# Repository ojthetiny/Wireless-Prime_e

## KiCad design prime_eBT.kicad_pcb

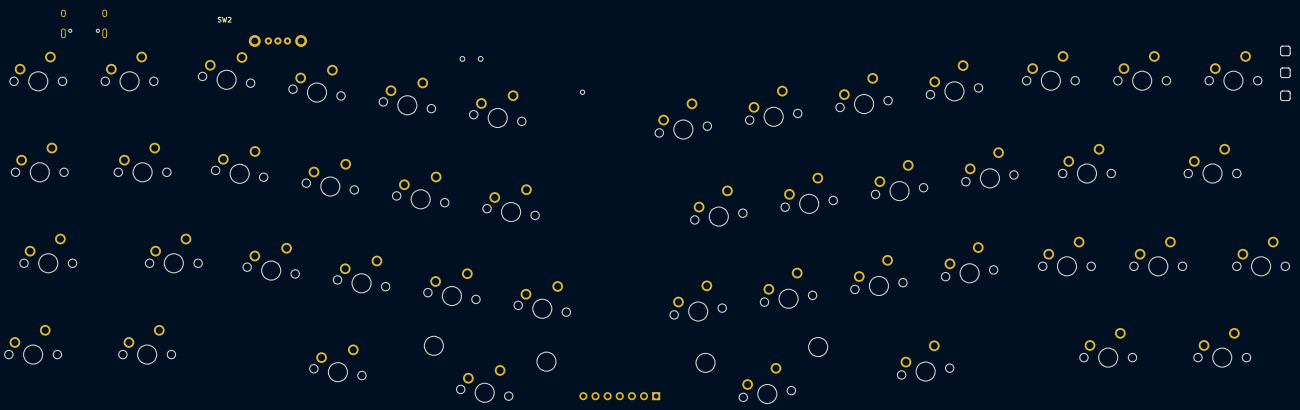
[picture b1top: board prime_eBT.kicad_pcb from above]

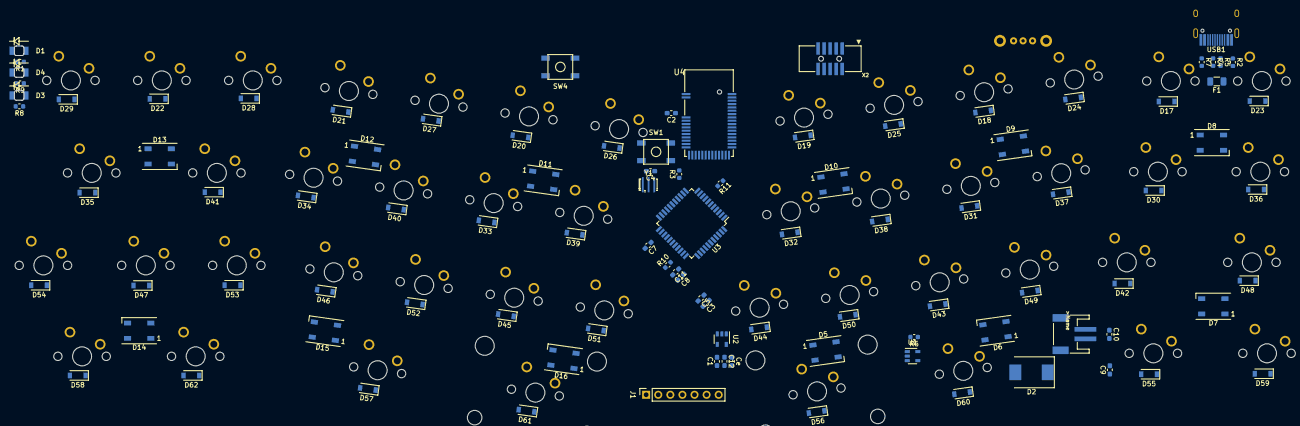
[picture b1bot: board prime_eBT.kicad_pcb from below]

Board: 2 copper layers, 144 parts (97 on the bottom side), 112 nets, no tracks yet.

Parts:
C1: 470pF; C_0603_1608Metric_Pad1.05x0.95mm_HandSolder
C2: 10uF; C_0603_1608Metric_Pad1.05x0.95mm_HandSolder
C3, C4, C5, C7: 0.1uF; C_0603_1608Metric_Pad1.05x0.95mm_HandSolder
C8, C9, C10: 4.7uF; C_0603_1608Metric_Pad1.05x0.95mm_HandSolder
C11, C12: 1uF; C_0603_1608Metric_Pad1.05x0.95mm_HandSolder
Ce: 10uF; C_0603_1608Metric_Pad1.05x0.95mm_HandSolder
D1, D3, D4: LED; IN-S124BR_LED
D2: B340; D_SMC
D5, D6, D7, D8, D9, D10, D11, D12, D13, D14, D15, D16: WS2812B; LED_WS2812B_PLCC4_5.0x5.0mm_P3.2mm
D17, D18, D19, D20, D21, D22, D23, D24, D25, D26, D27, D28, D29, D30, D31, D32, D33, D34, D35, D36, D37, D38, D39, D40, D41, D42, D43, D44, D45, D46, D47, D48, D49, D50, D51, D52, D53, D54, D55, D56, D57, D58, D59, D60, D61, D62: D_Small; D_SOD-123
F1: 500mA; Fuse_1206_3216Metric
J1: Connector_Generic_Conn_01x07; PinSocket_1x07_P2.54mm_Vertical
MX1, MX2, MX3, MX4, MX5, MX6, MX7, MX8, MX9, MX10, MX11, MX12, MX13, MX15, MX16, MX17, MX18, MX19, MX20, MX21, MX22, MX23, MX24, MX27, MX28, MX29, MX30, MX31, MX32, MX33, MX34, MX35, MX36, MX37: MX-NoLED; MXOnly-1U-NoLED
MX14, MX38, MX39, MX40, MX41, MX44, MX45, MX46: MX-NoLED; MXOnly-1.25U-NoLED
MX25, MX26: MX-NoLED; MXOnly-1.75U-NoLED
MX42: MX-NoLED; MXOnly-2U-ReversedStabilizers-NoLED
MX43: MX-NoLED; MXOnly-2.25U-ReversedStabilizers-NoLED
R1, R8, R9: 2.2K; R_0603_1608Metric
R2, R7: 5.1K; R_0603_1608Metric
R3, R6, R10: 10K; R_0603_1608Metric
R4, R5: 22; R_0603_1608Metric
R11: 500; R_0603_1608Metric
SW1, SW4: SW_PUSH-keyboard_parts; SKQG-1155865
SW2: Switch_SW_SPDT; SW_EG1213
U1: MCP73831-2-OT; SOT-23-5
U2: MIC5219-3.3YM5; SOT-23-5
U3: ATmega32U4-AU-MCU_Microchip_ATmega; TQFP-44_10x10mm_P0.8mm
U4: Adafruit-Feather-32u4-Bluefruit-LE_mod2-rescue_NR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; BLE_MODULE_RAYTAC_MDBT40
USB1: HRO-TYPE-C-31-M-12-Type-C; HRO-TYPE-C-31-M-12-HandSoldering
X1: CON_JST_PH_2PIN-Adafruit_Feather_32u4_Bluefruit_L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; JSTPH2
X2: JTAG-CORTEXBOXPOSTS-keyboard_parts; 2X05_1.27MM_BOX_POSTS
Y1: 16MHz; Resonator_SMD_muRata_CSTxExxV-3Pin_3.0x1.1mm_HandSoldering

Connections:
+3V3: C2.1, C3.1, C4.1, C5.1, C7.1, C8.1, C11.1, C12.1, Ce.1, J1.1, R3.1, U2.5, U3.6, U3.14, U3.24, U3.34, U3.42, U3.44, U4.3, U4.14, X2.1
+BATT: C10.1, X1.2
BLE_CS: U3.28, U4.7
BLE_IRQ: U3.1, U4.8
CONNECTED: R9.1, U4.39
DBUS+: R5.2, U3.4
DBUS-: R4.2, U3.3
DFU: SW4.2, U4.24
GND: C1.1, C2.2, C3.2, C4.2, C5.2, C7.2, C8.2, C9.2, C10.2, C11.2, C12.2, Ce.2, D3.1, D4.1, J1.2, R6.2, R10.1, SW1.1, SW2.1, SW4.1, U1.2, U2.2, U3.5, U3.15, U3.23, U3.35, U3.43, U4.1, U4.2, U4.13, U4.16, U4.25, U4.42, USB1.1, USB1.12, USB1.13, X1.1, X2.3, X2.5, X2.7, X2.9, Y1.2
MISO: U3.11, U4.5
MODE: R8.1, U4.38
MOSI: U3.10, U4.6
unnamed: C1.2, U2.4
unnamed: D1.1, R1.2
unnamed: D2.2, U1.3
unnamed: D3.2, R8.2
unnamed: D4.2, R9.2
unnamed: D5.2, D6.4
unnamed: D5.4, R11.1
unnamed: D6.2, D7.4
unnamed: D7.2, D8.4
unnamed: D8.2, D9.4
unnamed: D10.2, D11.4
unnamed: D9.2, D10.4
unnamed: D11.2, D12.4
unnamed: D12.2, D13.4
unnamed: D13.2, D14.4
unnamed: D14.2, D15.4
unnamed: D15.2, D16.4
unnamed: D17.2, MX2.2
unnamed: D18.2, MX4.2
unnamed: D19.2, MX6.2
unnamed: D20.2, MX8.2
unnamed: D21.2, MX10.2
unnamed: D22.2, MX12.2
unnamed: D23.2, MX1.2
unnamed: D24.2, MX3.2
unnamed: D25.2, MX5.2
unnamed: D26.2, MX7.2
unnamed: D27.2, MX9.2
unnamed: D28.2, MX11.2
unnamed: D29.2, MX13.2
unnamed: D30.2, MX15.2
unnamed: D31.2, MX17.2
unnamed: D32.2, MX19.2
unnamed: D33.2, MX21.2
unnamed: D34.2, MX23.2
unnamed: D35.2, MX25.2
unnamed: D36.2, MX14.2
unnamed: D37.2, MX16.2
unnamed: D38.2, MX18.2
unnamed: D39.2, MX20.2
unnamed: D40.2, MX22.2
unnamed: D41.2, MX24.2
unnamed: D42.2, MX27.2
unnamed: D43.2, MX29.2
unnamed: D44.2, MX31.2
unnamed: D45.2, MX33.2
unnamed: D46.2, MX35.2
unnamed: D47.2, MX37.2
unnamed: D48.2, MX26.2
unnamed: D49.2, MX28.2
unnamed: D50.2, MX30.2
unnamed: D51.2, MX32.2
unnamed: D52.2, MX34.2
unnamed: D53.2, MX36.2
unnamed: D54.2, MX38.2
unnamed: D55.2, MX40.2
unnamed: D56.2, MX42.2
unnamed: D57.2, MX44.2
unnamed: D58.2, MX46.2
unnamed: D59.2, MX39.2
unnamed: D60.2, MX41.2
unnamed: D61.2, MX43.2
unnamed: D62.2, MX45.2
unnamed: F1.1, USB1.2, USB1.11
unnamed: MX1.1, MX2.1, MX14.1, MX15.1, MX26.1, MX27.1, MX39.1, MX40.1
unnamed: MX9.1, MX10.1, MX22.1, MX23.1, MX34.1, MX35.1, MX44.1
unnamed: MX11.1, MX12.1, MX24.1, MX36.1, MX37.1, MX45.1
unnamed: MX13.1, MX25.1, MX38.1, MX46.1
unnamed: MX3.1, MX4.1, MX16.1, MX17.1, MX28.1, MX29.1, MX41.1
unnamed: MX5.1, MX6.1, MX18.1, MX19.1, MX30.1, MX31.1, MX42.1
unnamed: MX7.1, MX8.1, MX20.1, MX21.1, MX32.1, MX33.1, MX43.1
unnamed: R1.1, U1.1
unnamed: R2.1, USB1.4
unnamed: R2.2, R7.2
unnamed: R3.2, SW1.2, U3.13
unnamed: R4.1, USB1.5, USB1.7
unnamed: R5.1, USB1.6, USB1.8
unnamed: R6.1, U1.5
unnamed: R7.1, USB1.10
unnamed: R10.2, U3.33
unnamed: SW2.2, U2.3
unnamed: U3.16, Y1.3
unnamed: U3.17, Y1.1
RGB1: R11.2, U3.8
ROW0: D59.1, D60.1, D61.1, D62.1
ROW1: D48.1, D49.1, D50.1, D51.1, D52.1, D53.1, D54.1
ROW2: D36.1, D37.1, D38.1, D39.1, D40.1, D41.1
ROW3: D23.1, D24.1, D25.1, D26.1, D27.1, D28.1, D29.1
ROW4: D17.1, D18.1, D19.1, D20.1, D21.1, D22.1
ROW5: D30.1, D31.1, D32.1, D33.1, D34.1, D35.1
ROW6: D42.1, D43.1, D44.1, D45.1, D46.1, D47.1
ROW7: D55.1, D56.1, D57.1, D58.1
SCK: U3.9, U4.4
SWCLK: U4.36, X2.4
SWDIO_RST: U4.35, X2.2
TCK: J1.7, U3.39
TDI: J1.4, U3.36
TDO: J1.5, U3.37
TMS: J1.6, U3.38
VBUS: C9.1, D1.2, D2.1, F1.2, SW2.3, U1.4, U2.1, U3.7

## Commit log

2020-10-05 Schematic done, components laid out for pcb
